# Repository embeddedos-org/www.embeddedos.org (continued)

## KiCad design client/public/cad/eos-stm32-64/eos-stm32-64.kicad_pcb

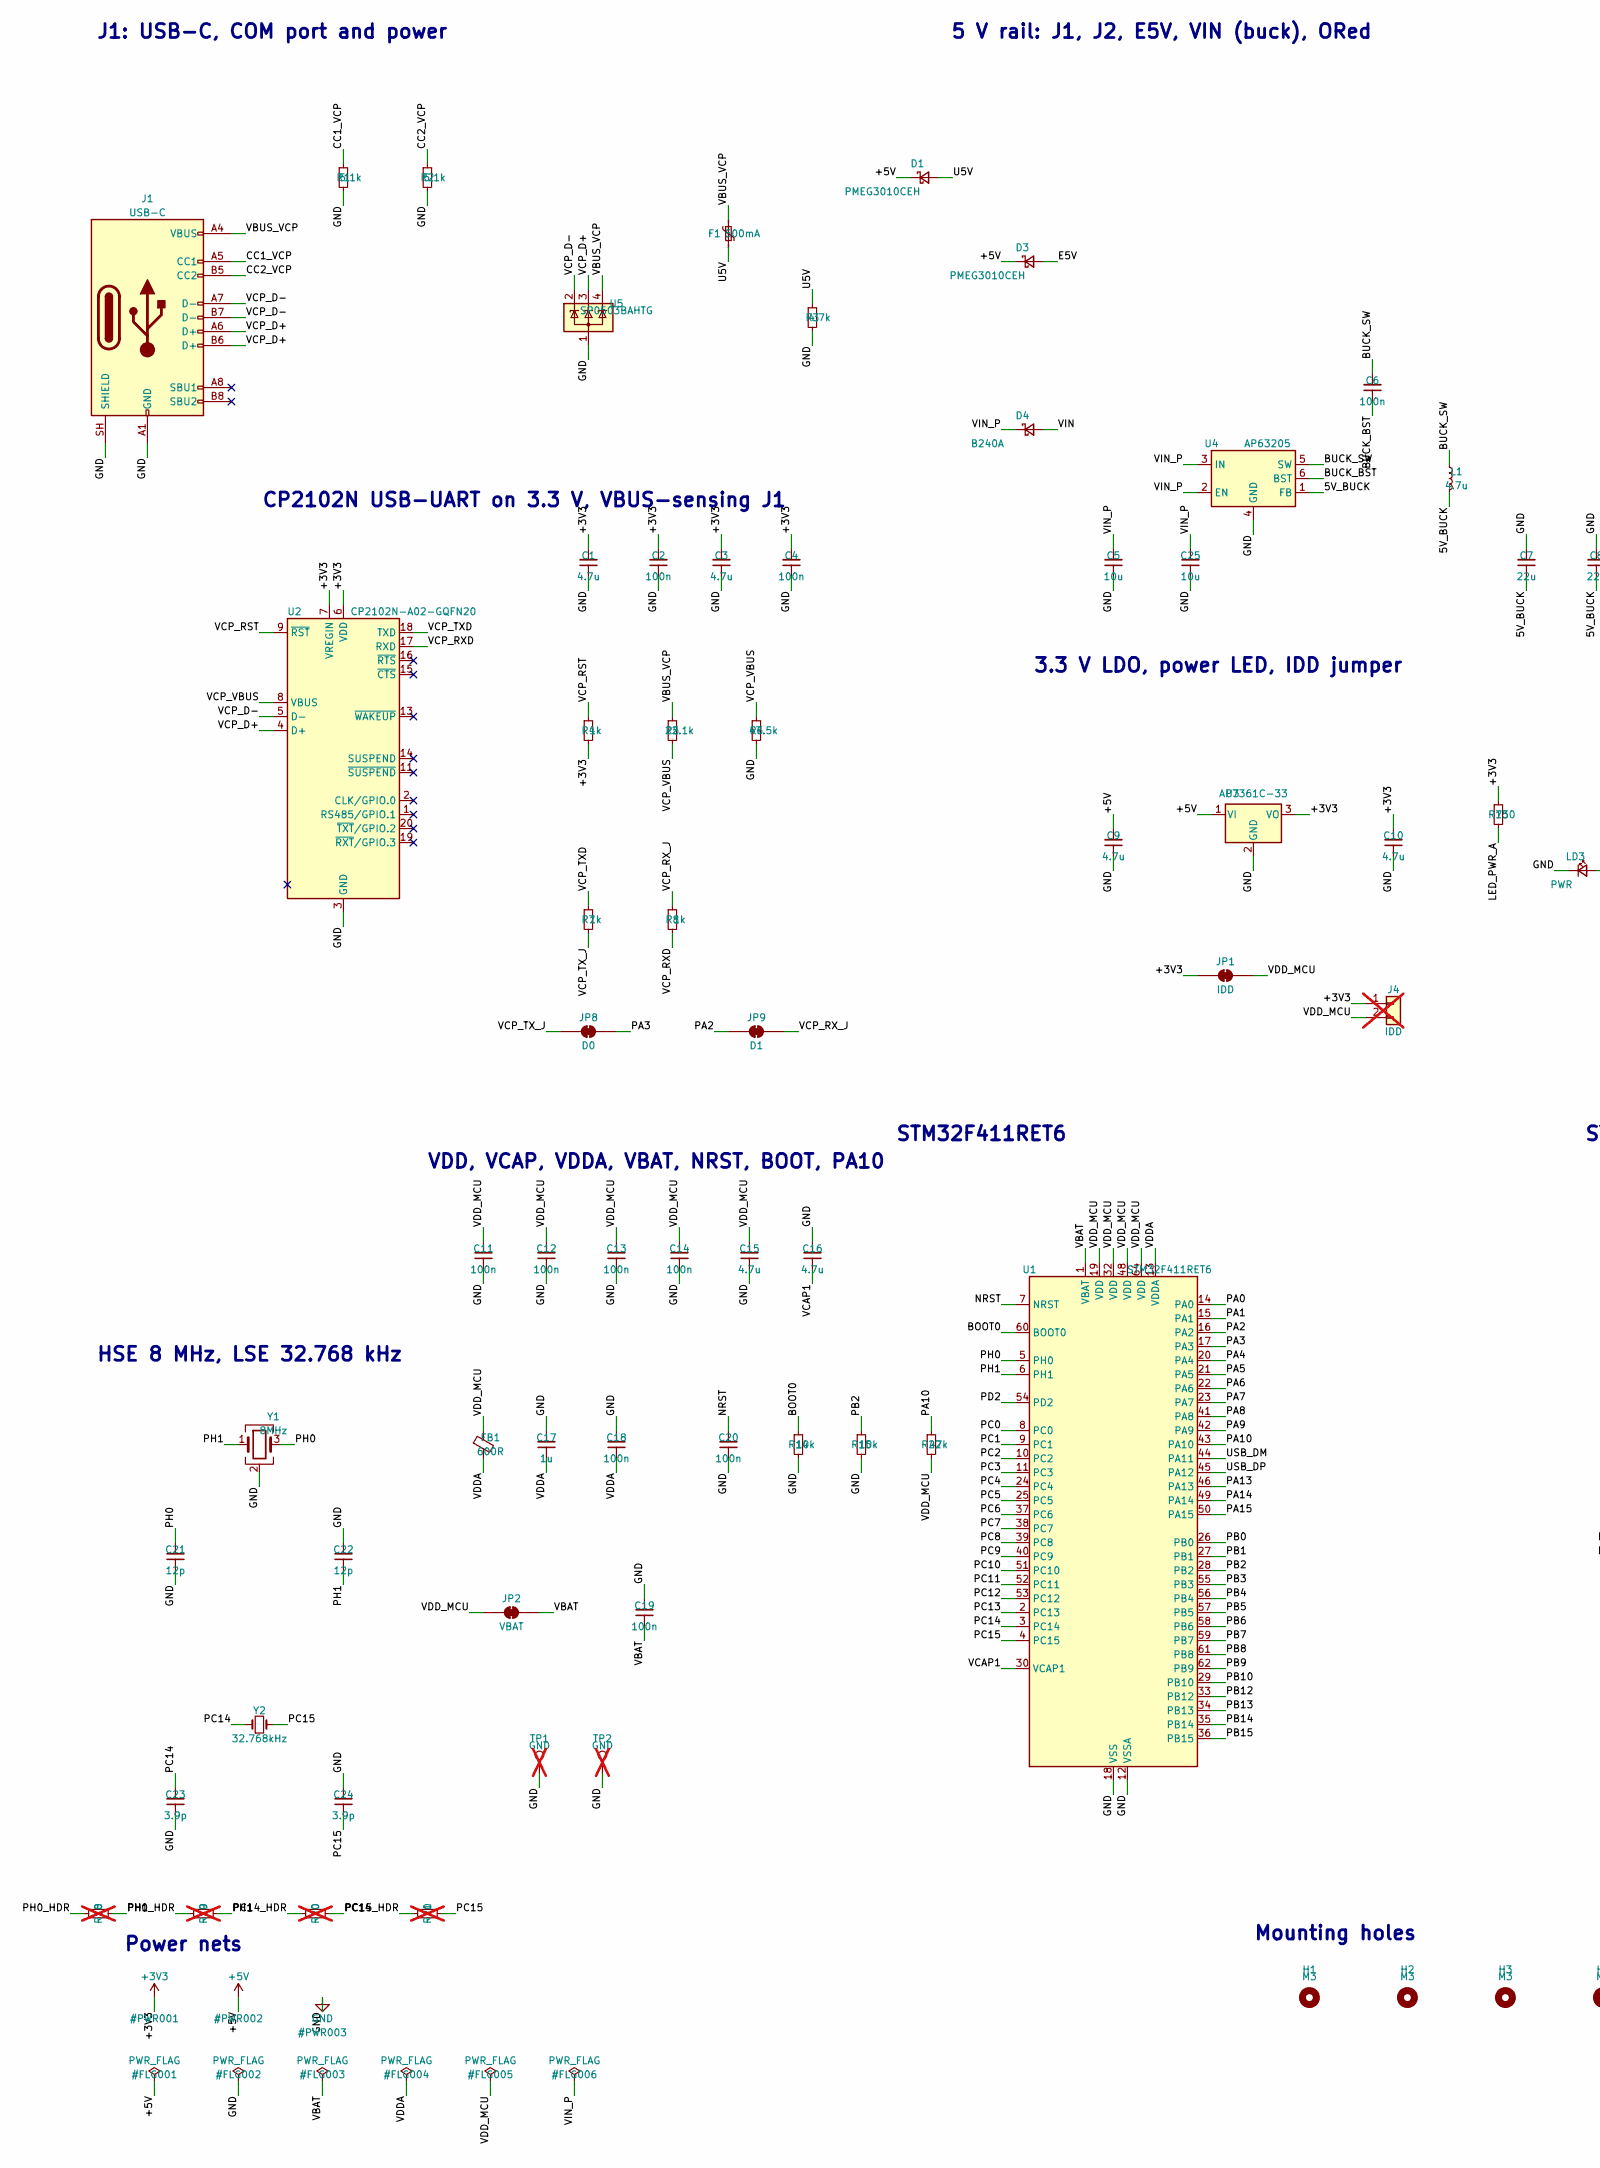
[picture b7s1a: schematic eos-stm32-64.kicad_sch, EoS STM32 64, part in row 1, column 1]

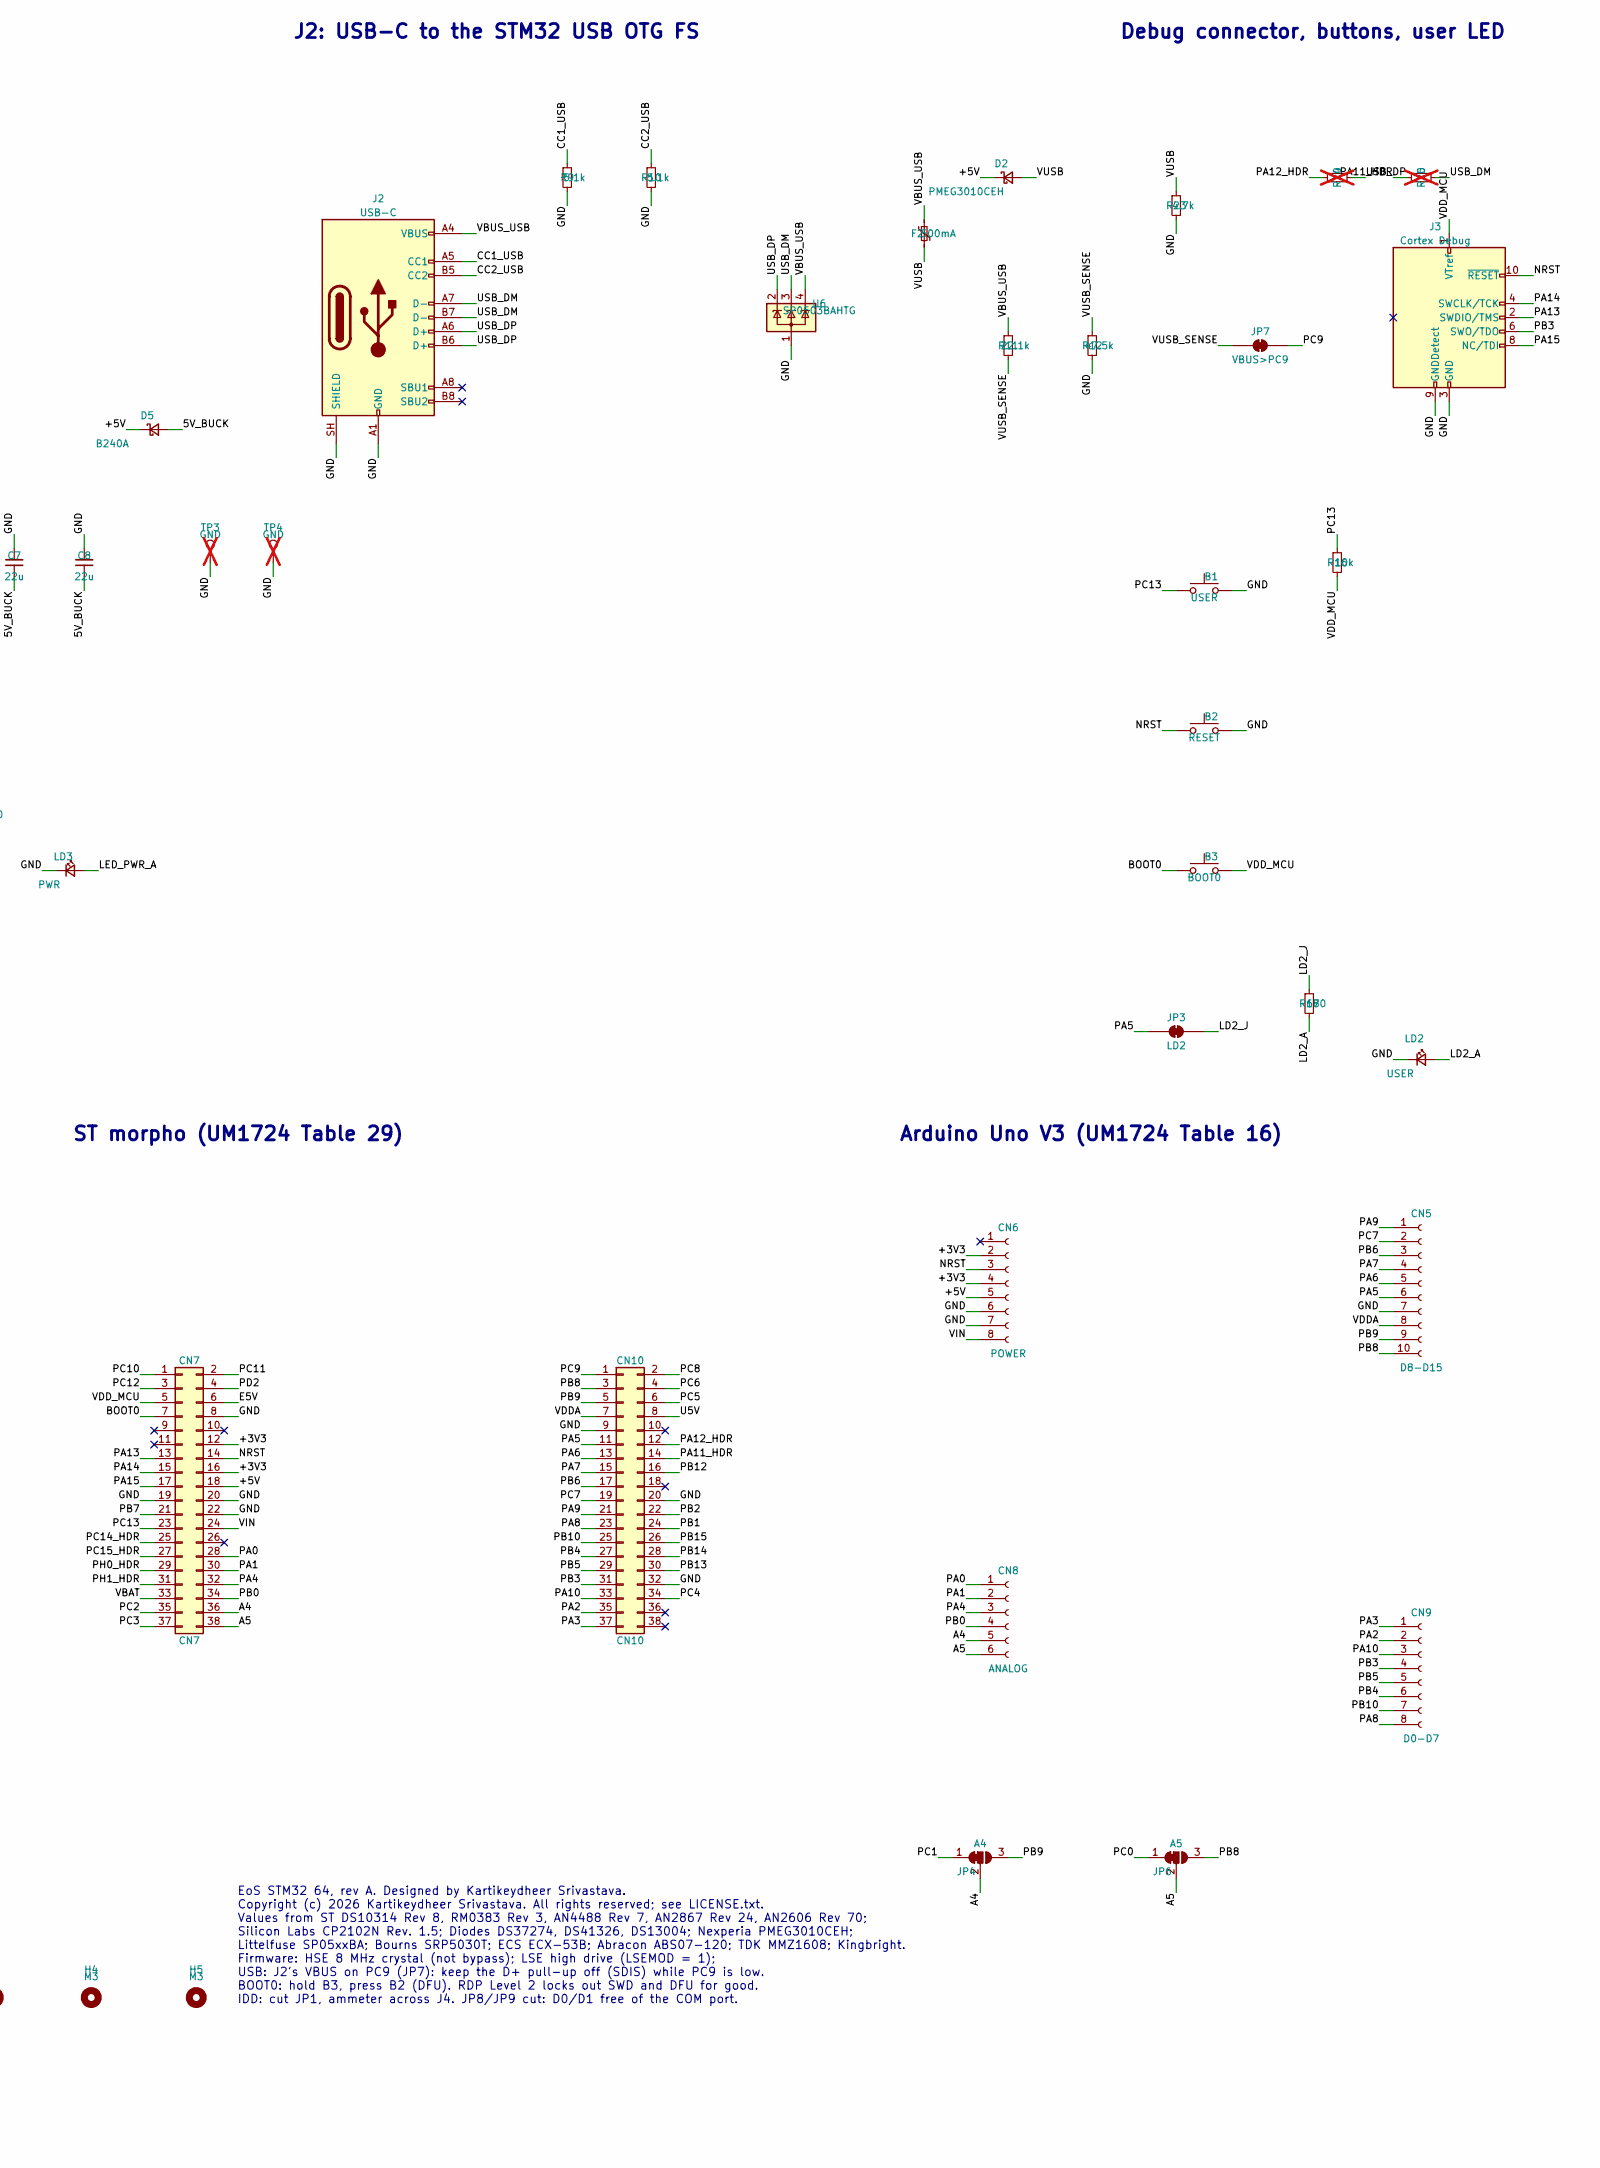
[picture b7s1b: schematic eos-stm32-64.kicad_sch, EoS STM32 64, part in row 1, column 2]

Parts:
B1: USER; SW_Push_1P1T_NO_CK_KMR2; MPN KMR221G LFS
B2: RESET; SW_Push_1P1T_NO_CK_KMR2; MPN KMR221G LFS
B3: BOOT0; SW_Push_1P1T_NO_CK_KMR2; MPN KMR221G LFS
C1, C3, C9, C10, C15, C16: 4.7u; C_0805_2012Metric; MPN CL21A475KAQNNNE
C2, C4, C11, C12, C13, C14, C18, C19, C20: 100n; C_0402_1005Metric; MPN CL05B104KO5NNNC
C5, C25: 10u; C_1206_3216Metric; MPN CL31A106KBHNNNE
C6: 100n; C_0402_1005Metric; MPN CL05B104KB54PNC
C7, C8: 22u; C_1206_3216Metric; MPN CL31A226KAHNNNE
C17: 1u; C_0402_1005Metric; MPN CL05A105KA5NQNC
C21, C22: 12p; C_0402_1005Metric; MPN CL05C120JB5NNNC
C23, C24: 3.9p; C_0402_1005Metric; MPN GRM1555C1H3R9CA01D
CN5: D8-D15; PinSocket_1x10_P2.54mm_Vertical; MPN SSW-110-01-T-S
CN6: POWER; PinSocket_1x08_P2.54mm_Vertical; MPN SSW-108-01-T-S
CN7: CN7; PinHeader_2x19_P2.54mm_Vertical; MPN TSW-119-07-L-D
CN8: ANALOG; PinSocket_1x06_P2.54mm_Vertical; MPN SSW-106-01-T-S
CN9: D0-D7; PinSocket_1x08_P2.54mm_Vertical; MPN SSW-108-01-T-S
CN10: CN10; PinHeader_2x19_P2.54mm_Vertical; MPN TSW-119-07-L-D
D1, D2, D3: PMEG3010CEH; D_SOD-123F; MPN PMEG3010CEH,115
D4, D5: B240A; D_SMA; MPN B240A-13-F
F1, F2: 500mA; Fuse_1206_3216Metric; MPN 1206L050YR
FB1: 600R; L_0603_1608Metric; MPN MMZ1608B601CTAH0
H1, H2, H3, H4, H5: M3; MountingHole_3.2mm_M3_ISO14580
J1, J2: USB-C; USB_C_Receptacle_HRO_TYPE-C-31-M-12; MPN TYPE-C-31-M-12
J3: Cortex Debug; PinHeader_2x05_P1.27mm_Vertical_SMD; MPN FTSH-105-01-L-DV-K
J4: IDD; PinHeader_1x02_P2.54mm_Vertical; not fitted
JP1: IDD; SolderJumper-2_P1.3mm_Bridged_RoundedPad1.0x1.5mm
JP2: VBAT; SolderJumper-2_P1.3mm_Bridged_RoundedPad1.0x1.5mm
JP3: LD2; SolderJumper-2_P1.3mm_Bridged_RoundedPad1.0x1.5mm
JP4: A4; SolderJumper-3_P1.3mm_Bridged12_RoundedPad1.0x1.5mm
JP6: A5; SolderJumper-3_P1.3mm_Bridged12_RoundedPad1.0x1.5mm
JP7: VBUS>PC9; SolderJumper-2_P1.3mm_Bridged_RoundedPad1.0x1.5mm
JP8: D0; SolderJumper-2_P1.3mm_Bridged_RoundedPad1.0x1.5mm
JP9: D1; SolderJumper-2_P1.3mm_Bridged_RoundedPad1.0x1.5mm
L1: 4.7u; L_Bourns_SRP5030T; MPN SRP5030T-4R7M
LD2: USER; LED_0603_1608Metric; MPN APTD1608LCGCK
LD3: PWR; LED_0603_1608Metric; MPN APTD1608LSURCK
R1, R2, R9, R10: 5.1k; R_0402_1005Metric; MPN RC0402FR-075K1L
R3, R23: 4.7k; R_0402_1005Metric; MPN RC0402FR-074K7L
R4, R7, R8: 1k; R_0402_1005Metric; MPN RC0402FR-071KL
R5, R11: 22.1k; R_0402_1005Metric; MPN RC0402FR-0722K1L
R6, R12: 47.5k; R_0402_1005Metric; MPN RC0402FR-0747K5L
R13: 750; R_0402_1005Metric; MPN RC0402FR-07750RL
R14, R15, R16: 10k; R_0402_1005Metric; MPN RC0402FR-0710KL
R17: 680; R_0402_1005Metric; MPN RC0402FR-07680RL
R18, R19, R20, R21, R24, R25: 0; R_0402_1005Metric; not fitted
R22: 47k; R_0402_1005Metric; MPN RC0402FR-0747KL
TP1, TP2: GND; SolderWirePad_1x01_SMD_5x10mm; not fitted
TP3, TP4: GND; TestPoint_THTPad_D1.0mm_Drill0.5mm; not fitted
U1: STM32F411RET6; LQFP-64_10x10mm_P0.5mm; MPN STM32F411RET6
U2: CP2102N-A02-GQFN20; SiliconLabs_QFN-20-1EP_3x3mm_P0.5mm_EP1.8x1.8mm; MPN CP2102N-A02-GQFN20R
U3: AP7361C-33; SOT-223-3_TabPin2; MPN AP7361C-33E-13
U4: AP63205; TSOT-23-6; MPN AP63205WU-7
U5, U6: SP0503BAHTG; SOT-143; MPN SP0503BAHTG
Y1: 8MHz; Crystal_SMD_5032-4Pin_5.0x3.2mm; MPN ECS-80-10-30B-CWN-TR
Y2: 32.768kHz; Crystal_SMD_3215-2Pin_3.2x1.5mm; MPN ABS07-120-32.768KHZ-T

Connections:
+3V3: C1.1, C2.1, C3.1, C4.1, C10.1, CN6.2, CN6.4, CN7.12, CN7.16, J4.1, JP1.1 (A), R4.2, R13.1, U2.6 (VDD), U2.7 (VREGIN), U3.3 (VO)
+5V: C9.1, CN6.5, CN7.18, D1.1 (K), D2.1 (K), D3.1 (K), D5.1 (K), U3.1 (VI)
/5V_BUCK: C7.2, C8.2, D5.2 (A), L1.2, U4.1 (FB)
/A4: CN7.36, CN8.5, JP4.2 (C)
/A5: CN7.38, CN8.6, JP6.2 (C)
/BOOT0: B3.1, CN7.7, R14.1, U1.60 (BOOT0)
/BUCK_BST: C6.2, U4.6 (BST)
/BUCK_SW: C6.1, L1.1, U4.5 (SW)
/CC1_USB: J2.A5 (CC1), R9.1
/CC1_VCP: J1.A5 (CC1), R1.1
/CC2_USB: J2.B5 (CC2), R10.1
/CC2_VCP: J1.B5 (CC2), R2.1
/E5V: CN7.6, D3.2 (A)
/LD2_A: LD2.2 (A), R17.2
/LD2_J: JP3.2 (B), R17.1
/LED_PWR_A: LD3.2 (A), R13.2
/NRST: B2.1, C20.1, CN6.3, CN7.14, J3.10 (~RESET), U1.7 (NRST)
/PA0: CN7.28, CN8.1, U1.14 (PA0)
/PA1: CN7.30, CN8.2, U1.15 (PA1)
/PA2: CN9.2, CN10.35, JP9.1 (A), U1.16 (PA2)
/PA3: CN9.1, CN10.37, JP8.2 (B), U1.17 (PA3)
/PA4: CN7.32, CN8.3, U1.20 (PA4)
/PA5: CN5.6, CN10.11, JP3.1 (A), U1.21 (PA5)
/PA6: CN5.5, CN10.13, U1.22 (PA6)
/PA7: CN5.4, CN10.15, U1.23 (PA7)
/PA8: CN9.8, CN10.23, U1.41 (PA8)
/PA9: CN5.1, CN10.21, U1.42 (PA9)
/PA10: CN9.3, CN10.33, R22.1, U1.43 (PA10)
/PA11_HDR: CN10.14, R25.1
/PA12_HDR: CN10.12, R24.1
/PA13: CN7.13, J3.2 (SWDIO/TMS), U1.46 (PA13)
/PA14: CN7.15, J3.4 (SWCLK/TCK), U1.49 (PA14)
/PA15: CN7.17, J3.8 (NC/TDI), U1.50 (PA15)
/PB0: CN7.34, CN8.4, U1.26 (PB0)
/PB1: CN10.24, U1.27 (PB1)
/PB2: CN10.22, R15.1, U1.28 (PB2)
/PB3: CN9.4, CN10.31, J3.6 (SWO/TDO), U1.55 (PB3)
/PB4: CN9.6, CN10.27, U1.56 (PB4)
/PB5: CN9.5, CN10.29, U1.57 (PB5)
/PB6: CN5.3, CN10.17, U1.58 (PB6)
/PB7: CN7.21, U1.59 (PB7)
/PB8: CN5.10, CN10.3, JP6.3 (B), U1.61 (PB8)
/PB9: CN5.9, CN10.5, JP4.3 (B), U1.62 (PB9)
/PB10: CN9.7, CN10.25, U1.29 (PB10)
/PB12: CN10.16, U1.33 (PB12)
/PB13: CN10.30, U1.34 (PB13)
/PB14: CN10.28, U1.35 (PB14)
/PB15: CN10.26, U1.36 (PB15)
/PC0: JP6.1 (A), U1.8 (PC0)
/PC1: JP4.1 (A), U1.9 (PC1)
/PC2: CN7.35, U1.10 (PC2)
/PC3: CN7.37, U1.11 (PC3)
/PC4: CN10.34, U1.24 (PC4)
/PC5: CN10.6, U1.25 (PC5)
/PC6: CN10.4, U1.37 (PC6)
/PC7: CN5.2, CN10.19, U1.38 (PC7)
/PC8: CN10.2, U1.39 (PC8)
/PC9: CN10.1, JP7.2 (B), U1.40 (PC9)
/PC10: CN7.1, U1.51 (PC10)
/PC11: CN7.2, U1.52 (PC11)
/PC12: CN7.3, U1.53 (PC12)
/PC13: B1.1, CN7.23, R16.1, U1.2 (PC13)
/PC14: C23.1, R20.2, U1.3 (PC14), Y2.1
/PC14_HDR: CN7.25, R20.1
/PC15: C24.2, R21.2, U1.4 (PC15), Y2.2
/PC15_HDR: CN7.27, R21.1
/PD2: CN7.4, U1.54 (PD2)
/PH0: C21.1, R18.2, U1.5 (PH0), Y1.3
/PH0_HDR: CN7.29, R18.1
/PH1: C22.2, R19.2, U1.6 (PH1), Y1.1
/PH1_HDR: CN7.31, R19.1
/U5V: CN10.8, D1.2 (A), F1.2, R3.1
/USB_DM: J2.A7 (D-), J2.B7 (D-), R25.2, U1.44 (PA11), U6.3 (K)
/USB_DP: J2.A6 (D+), J2.B6 (D+), R24.2, U1.45 (PA12), U6.2 (K)
/VBAT: C19.2, CN7.33, JP2.2 (B), U1.1 (VBAT)
/VBUS_USB: F2.1, J2.A4 (VBUS), J2.A9 (VBUS), J2.B4 (VBUS), J2.B9 (VBUS), R11.1, U6.4 (K)
/VBUS_VCP: F1.1, J1.A4 (VBUS), J1.A9 (VBUS), J1.B4 (VBUS), J1.B9 (VBUS), R5.1, U5.4 (K)
/VCAP1: C16.2, U1.30 (VCAP1)
/VCP_D+: J1.A6 (D+), J1.B6 (D+), U2.4 (D+), U5.3 (K)
/VCP_D-: J1.A7 (D-), J1.B7 (D-), U2.5 (D-), U5.2 (K)
/VCP_RST: R4.1, U2.9 (~RST)
/VCP_RXD: R8.2, U2.17 (RXD)
/VCP_RX_J: JP9.2 (B), R8.1
/VCP_TXD: R7.1, U2.18 (TXD)
/VCP_TX_J: JP8.1 (A), R7.2
/VCP_VBUS: R5.2, R6.1, U2.8 (VBUS)
/VDDA: C17.2, C18.2, CN5.8, CN10.7, FB1.2, U1.13 (VDDA)
/VDD_MCU: B3.2, C11.1, C12.1, C13.1, C14.1, C15.1, CN7.5, FB1.1, J3.1 (VTref), J4.2, JP1.2 (B), JP2.1 (A), R16.2, R22.2, U1.19 (VDD), U1.32 (VDD), U1.48 (VDD), U1.64 (VDD)
/VIN: CN6.8, CN7.24, D4.2 (A)
/VIN_P: C5.1, C25.1, D4.1 (K), U4.2 (EN), U4.3 (IN)
/VUSB: D2.2 (A), F2.2, R23.1
/VUSB_SENSE: JP7.1 (A), R11.2, R12.1
GND: B1.2, B2.2, C1.2, C2.2, C3.2, C4.2, C5.2, C7.1, C8.1, C9.2, C10.2, C11.2, C12.2, C13.2, C14.2, C15.2, C16.1, C17.1, C18.1, C19.1, C20.2, C21.2, C22.1, C23.2, C24.1, C25.2, CN5.7, CN6.6, CN6.7, CN7.8, CN7.19, CN7.20, CN7.22, CN10.9, CN10.20, CN10.32, J1.A1 (GND), J1.A12 (GND), J1.B1 (GND), J1.B12 (GND), J1.SH (SHIELD), J2.A1 (GND), J2.A12 (GND), J2.B1 (GND), J2.B12 (GND), J2.SH (SHIELD), J3.3 (GND), J3.5 (GND), J3.9 (GNDDetect), LD2.1 (K), LD3.1 (K), R1.2, R2.2, R3.2, R6.2, R9.2, R10.2, R12.2, R14.2, R15.2, R23.2, TP1.1, TP2.1, TP3.1, TP4.1, U1.12 (VSSA), U1.18 (VSS), U1.31 (VSS), U1.47 (VSS), U1.63 (VSS), U2.3 (GND), U2.12 (GND), U2.21 (GND), U3.2 (GND), U4.4 (GND), U5.1 (A), U6.1 (A), Y1.2 (G), Y1.4 (G)

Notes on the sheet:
J1: USB-C, COM port and power
CP2102N USB-UART on 3.3 V, VBUS-sensing J1
5 V rail: J1, J2, E5V, VIN (buck), ORed
3.3 V LDO, power LED, IDD jumper
J2: USB-C to the STM32 USB OTG FS
Debug connector, buttons, user LED
STM32F411RET6
VDD, VCAP, VDDA, VBAT, NRST, BOOT, PA10
HSE 8 MHz, LSE 32.768 kHz
ST morpho (UM1724 Table 29)
Arduino Uno V3 (UM1724 Table 16)
Mounting holes
Power nets
EoS STM32 64, rev A. Designed by Kartikeydheer Srivastava. Copyright (c) 2026 Kartikeydheer Srivastava. All rights reserved; see LICENSE.txt. Values from ST DS10314 Rev 8, RM0383 Rev 3, AN4488 Rev 7, AN2867 Rev 24, AN2606 Rev 70; Silicon Labs CP2102N Rev. 1.5; Diodes DS37274, DS41326, DS13004; Nexp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

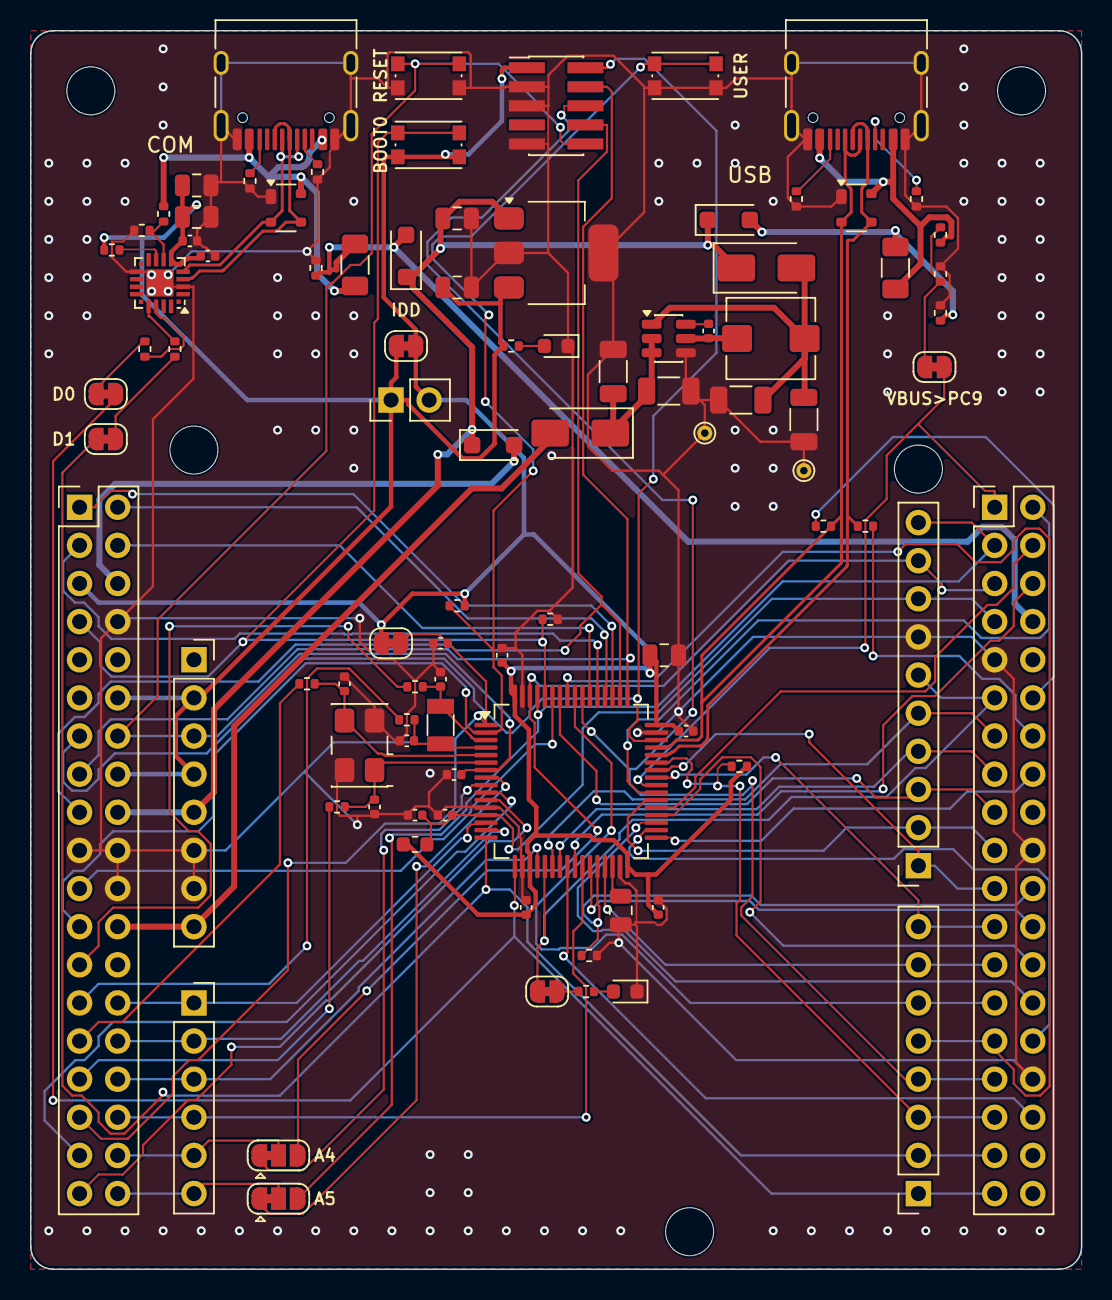
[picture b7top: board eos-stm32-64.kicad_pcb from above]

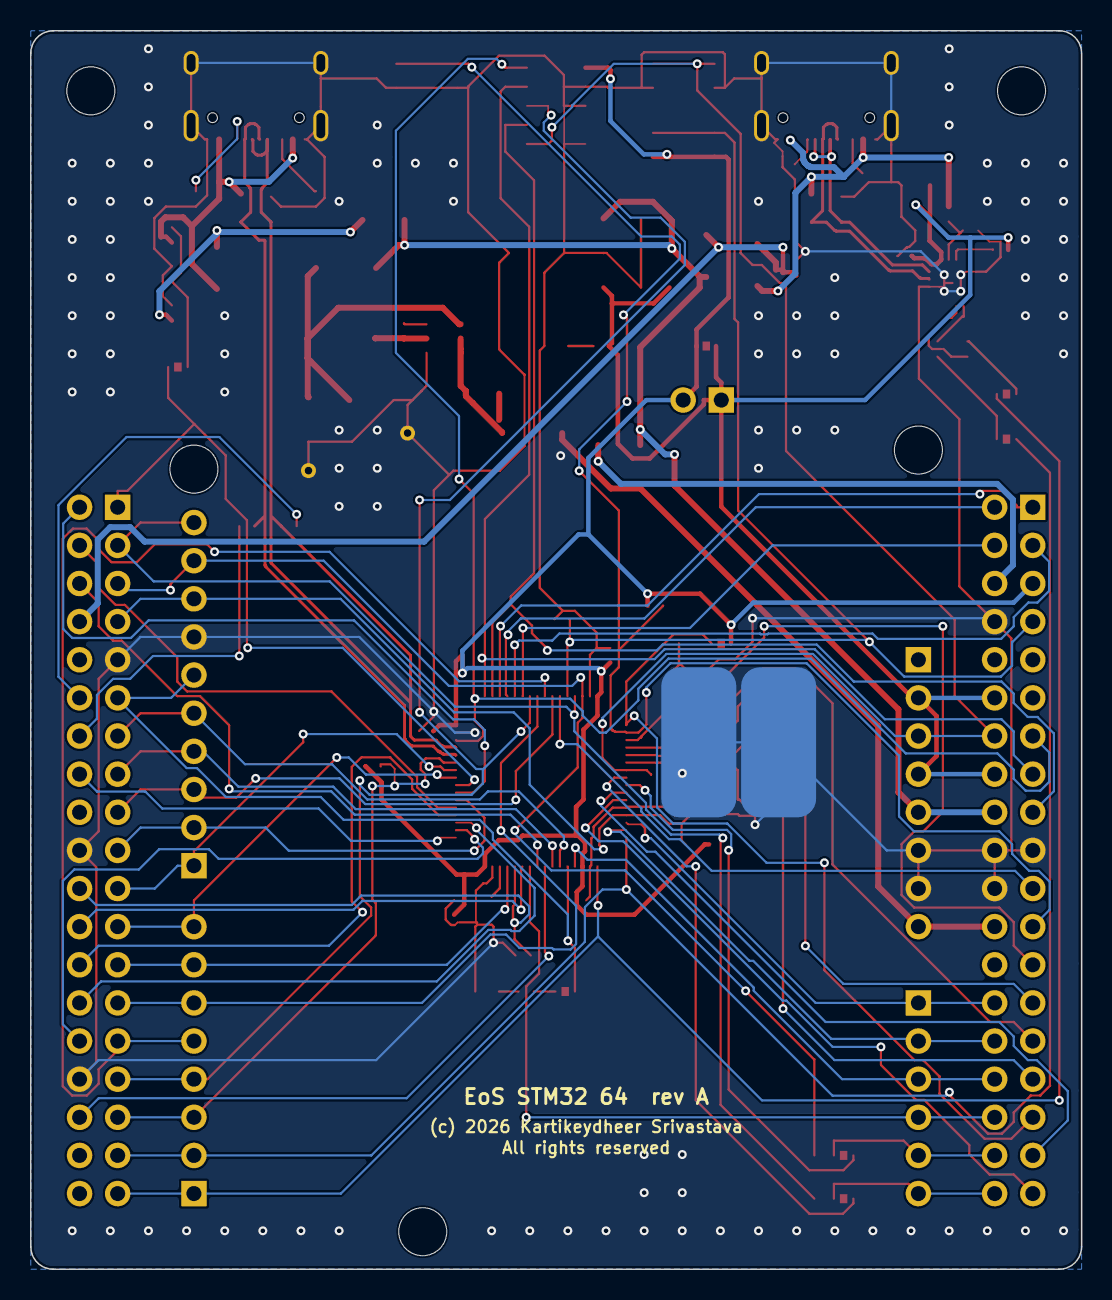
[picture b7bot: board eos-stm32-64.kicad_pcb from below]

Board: 2 copper layers, 70.0 x 82.5 mm, 99 parts (3 on the bottom side), 93 nets.

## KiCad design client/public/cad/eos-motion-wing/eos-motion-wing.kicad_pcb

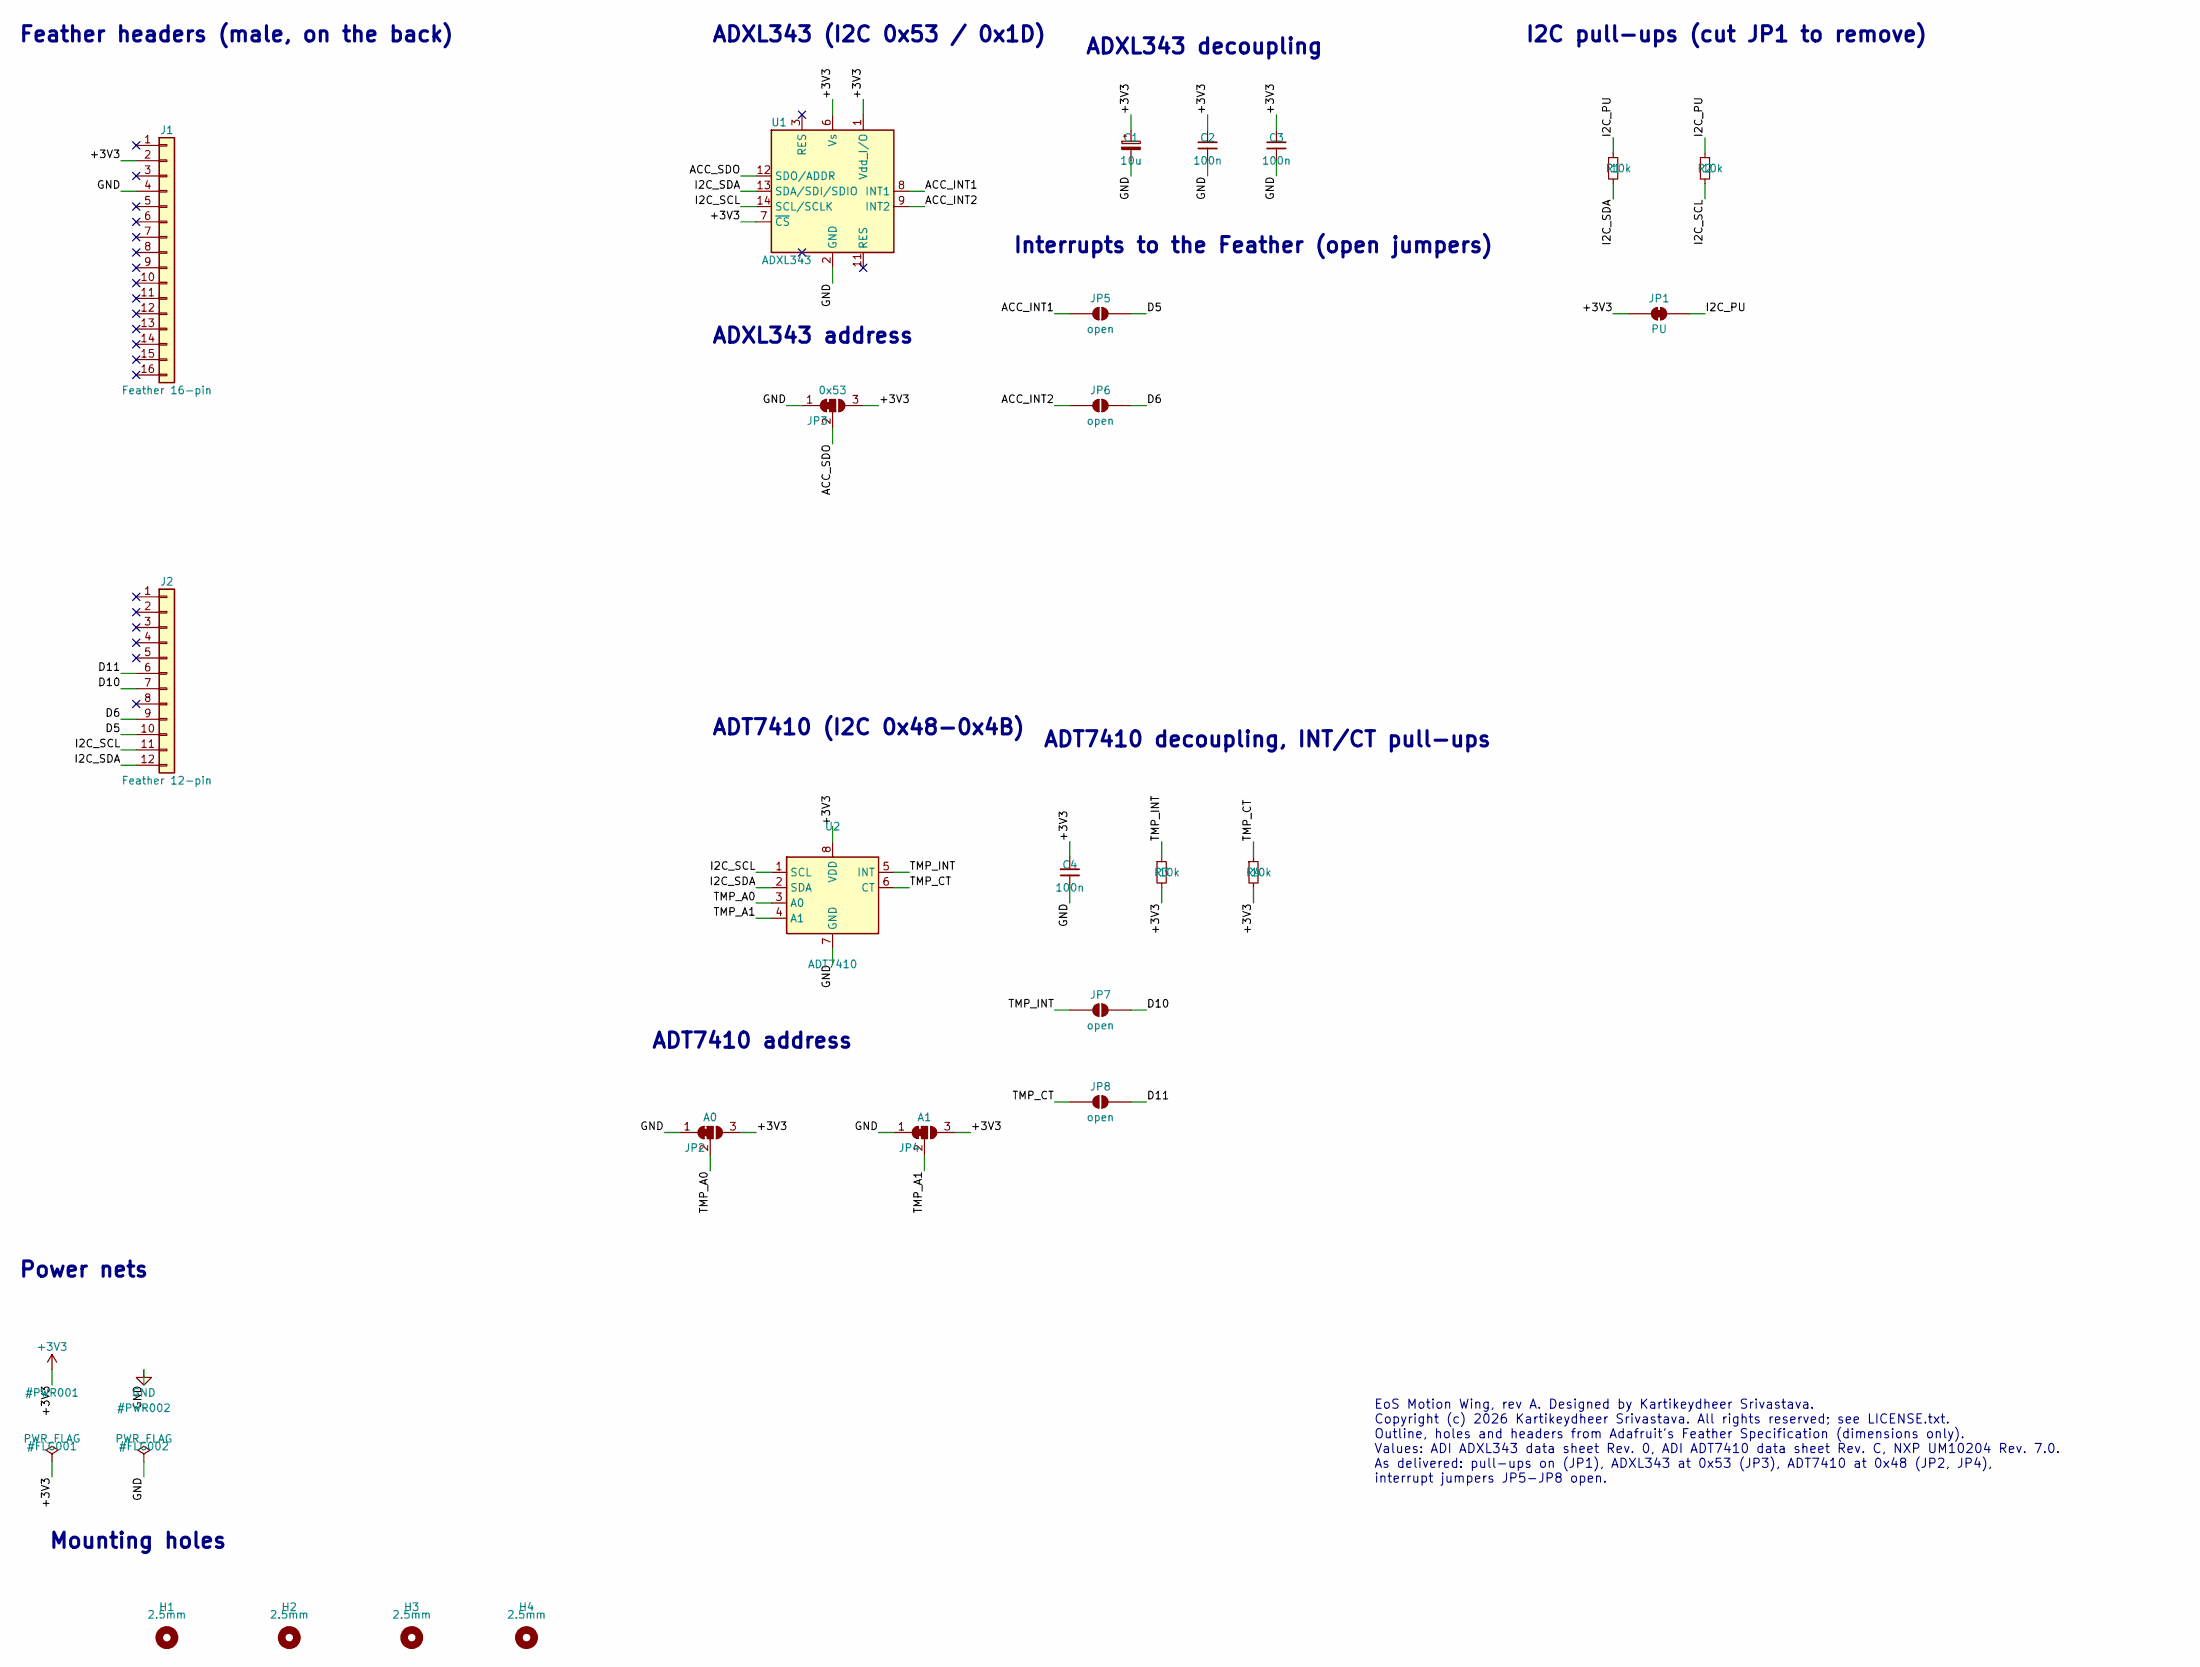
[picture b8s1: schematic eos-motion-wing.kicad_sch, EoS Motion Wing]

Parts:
C1: 10u; CP_EIA-3216-18_Kemet-A; MPN T491A106K016AT
C2, C3, C4: 100n; C_0603_1608Metric
H1, H2, H3, H4: 2.5mm; MountingHole_2.5mm
J1: Feather 16-pin; PinHeader_1x16_P2.54mm_Vertical; MPN 61301611121
J2: Feather 12-pin; PinHeader_1x12_P2.54mm_Vertical; MPN 61301211121
JP1: PU; SolderJumper-2_P1.3mm_Bridged_RoundedPad1.0x1.5mm
JP2: A0; SolderJumper-3_P1.3mm_Bridged12_RoundedPad1.0x1.5mm
JP3: 0x53; SolderJumper-3_P1.3mm_Bridged12_RoundedPad1.0x1.5mm
JP4: A1; SolderJumper-3_P1.3mm_Bridged12_RoundedPad1.0x1.5mm
JP5, JP6, JP7, JP8: open; SolderJumper-2_P1.3mm_Open_RoundedPad1.0x1.5mm
R1, R2, R3, R4: 10k; R_0603_1608Metric
U1: ADXL343; LGA-14_3x5mm_P0.8mm_LayoutBorder1x6y; MPN ADXL343BCCZ-RL7
U2: ADT7410; SOIC-8_3.9x4.9mm_P1.27mm; MPN ADT7410TRZ

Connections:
+3V3: C1.1, C2.1, C3.1, C4.1, J1.2, JP1.1 (A), JP2.3 (B), JP3.3 (B), JP4.3 (B), R3.2, R4.2, U1.1 (Vdd_I/O), U1.6 (Vs), U1.7 (~CS), U2.8 (VDD)
/ACC_INT1: JP5.1 (A), U1.8 (INT1)
/ACC_INT2: JP6.1 (A), U1.9 (INT2)
/ACC_SDO: JP3.2 (C), U1.12 (SDO/ADDR)
/D5: J2.10, JP5.2 (B)
/D6: J2.9, JP6.2 (B)
/D10: J2.7, JP7.2 (B)
/D11: J2.6, JP8.2 (B)
/I2C_PU: JP1.2 (B), R1.1, R2.1
/I2C_SCL: J2.11, R2.2, U1.14 (SCL/SCLK), U2.1 (SCL)
/I2C_SDA: J2.12, R1.2, U1.13 (SDA/SDI/SDIO), U2.2 (SDA)
/TMP_A0: JP2.2 (C), U2.3 (A0)
/TMP_A1: JP4.2 (C), U2.4 (A1)
/TMP_CT: JP8.1 (A), R4.1, U2.6 (CT)
/TMP_INT: JP7.1 (A), R3.1, U2.5 (INT)
GND: C1.2, C2.2, C3.2, C4.2, J1.4, JP2.1 (A), JP3.1 (A), JP4.1 (A), U1.2 (GND), U1.4 (GND), U1.5 (GND), U2.7 (GND)

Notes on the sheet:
Feather headers (male, on the back)
ADXL343 (I2C 0x53 / 0x1D)
ADXL343 decoupling
ADXL343 address
Interrupts to the Feather (open jumpers)
ADT7410 (I2C 0x48-0x4B)
ADT7410 decoupling, INT/CT pull-ups
ADT7410 address
I2C pull-ups (cut JP1 to remove)
Mounting holes
Power nets
EoS Motion Wing, rev A. Designed by Kartikeydheer Srivastava. Copyright (c) 2026 Kartikeydheer Srivastava. All rights reserved; see LICENSE.txt. Outline, holes and headers from Adafruit's Feather Specification (dimensions only). Values: ADI ADXL343 data sheet Rev. 0, ADI ADT7410 data sheet Rev. C, 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

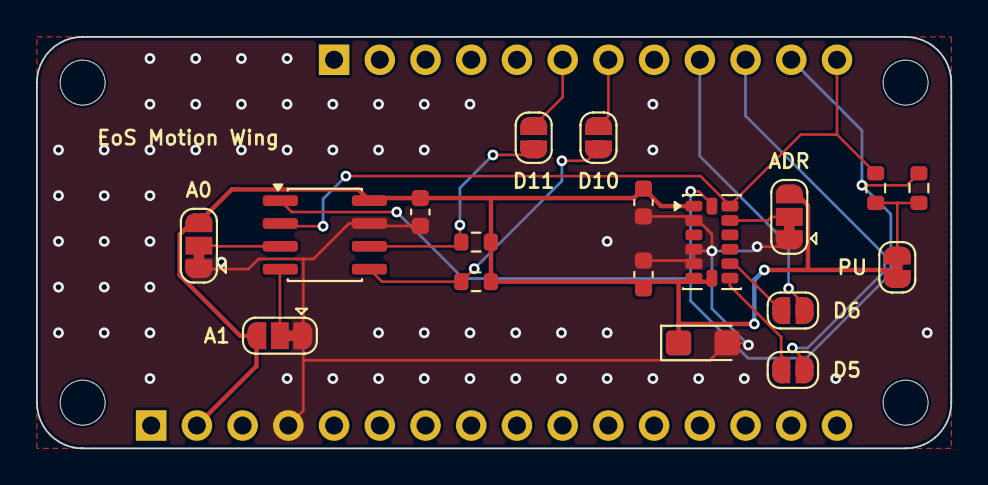
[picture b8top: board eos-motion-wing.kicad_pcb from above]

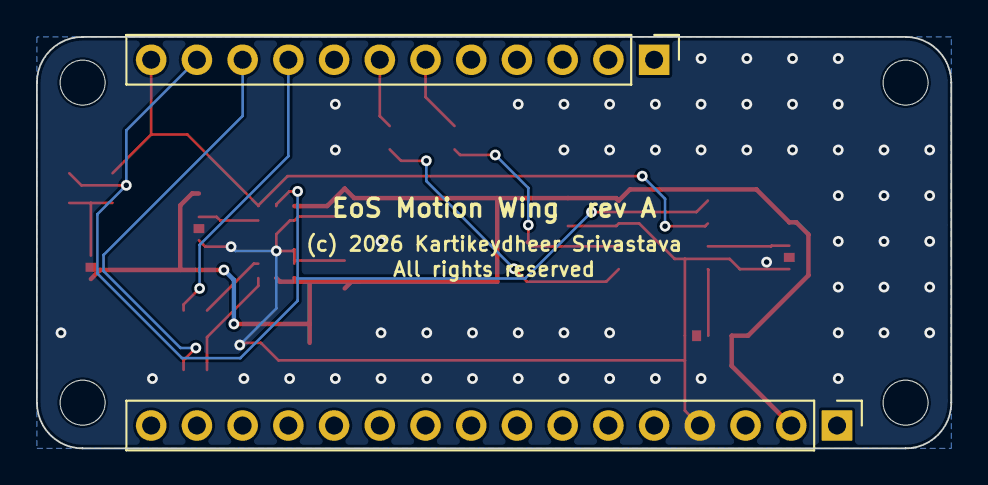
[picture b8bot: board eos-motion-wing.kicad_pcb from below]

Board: 2 copper layers, 50.8 x 22.9 mm, 24 parts (2 on the bottom side), 16 nets.
